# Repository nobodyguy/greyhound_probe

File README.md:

# Greyhound probe
Greyhound probe is a fast and efficient Black Magic Probe compatible programmer and debugger

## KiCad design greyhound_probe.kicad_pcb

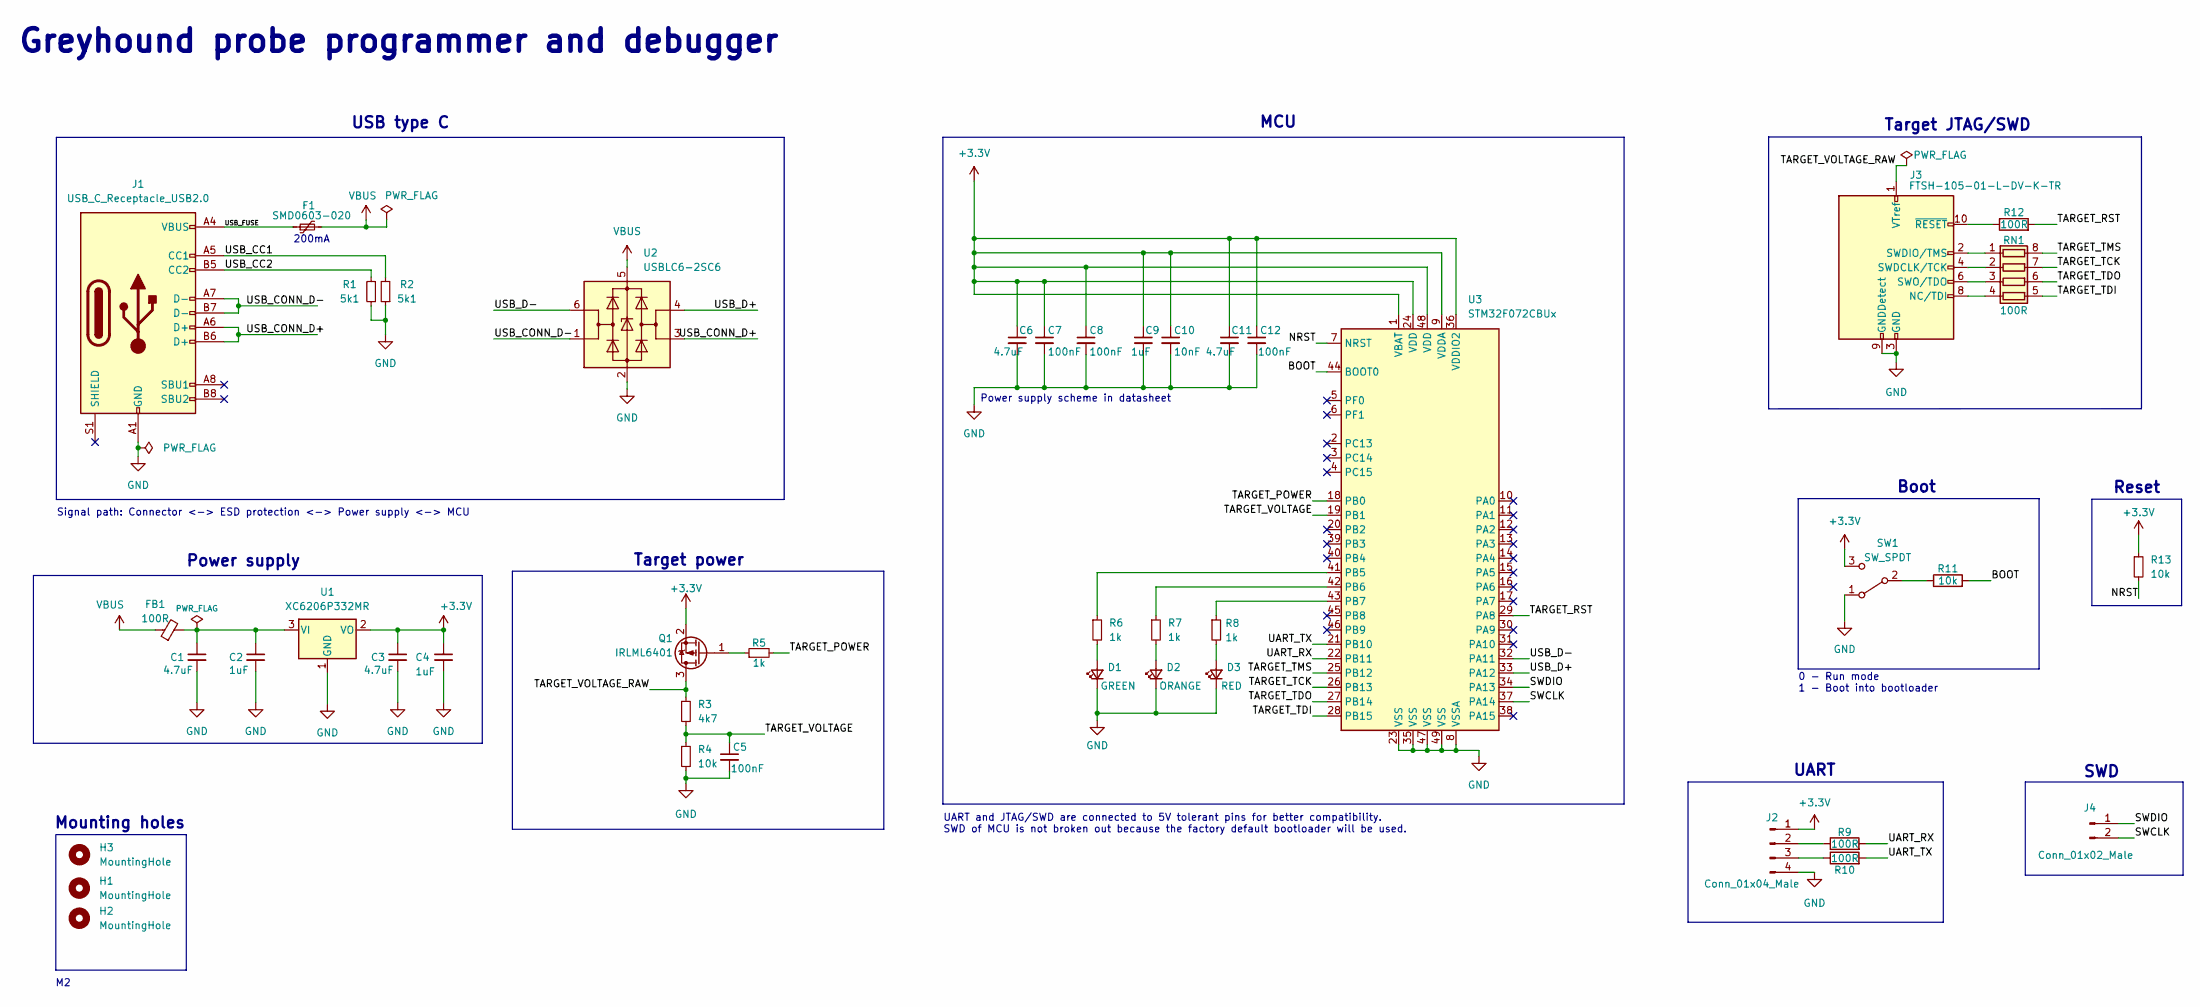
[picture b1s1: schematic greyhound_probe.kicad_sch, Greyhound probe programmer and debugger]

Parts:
C1, C3: 4.7uF; C_0603_1608Metric; LCSC Part C1592
C2, C4, C9: 1uF; C_0603_1608Metric; LCSC Part C1592
C5, C7, C8, C12: 100nF; C_0603_1608Metric; LCSC Part C66501
C6, C11: 4.7uF; C_0603_1608Metric; LCSC Part C8032
C10: 10nF; C_0603_1608Metric; LCSC Part C1589
D1: GREEN; D_0603_1608Metric; LCSC Part C72043
D2: ORANGE; D_0603_1608Metric; LCSC Part C146215
D3: RED; D_0603_1608Metric; LCSC Part C72044
F1: SMD0603-020; Fuse_0603_1608Metric; LCSC Part C2760255
FB1: 100R; L_0603_1608Metric; LCSC Part C74325
H1, H2, H3: MountingHole; MountingHole_2.2mm_M2
J1: USB_C_Receptacle_USB2.0; USB_C_Receptacle_HRO_TYPE-C-31-M-12; LCSC Part C165948
J2: Conn_01x04_Male; PinHeader_1x04_P2.54mm_Vertical; LCSC Part C2935910
J3: FTSH-105-01-L-DV-K-TR; PinHeader_2x05_P1.27mm_Vertical_SMD; LCSC Part C448647
J4: Conn_01x02_Male; PinHeader_1x02_P2.54mm_Vertical
Q1: IRLML6401; SOT-23; LCSC Part C518776
R1, R2: 5k1; R_0603_1608Metric; LCSC Part C105580
R3: 4k7; R_0603_1608Metric; LCSC Part C105428
R4, R13: 10k; R_0603_1608Metric
R5, R6, R7, R8: 1k; R_0603_1608Metric; LCSC Part C22548
R9, R10, R12: 100R; R_0603_1608Metric; LCSC Part C105588
R11: 10k; R_0603_1608Metric; LCSC Part C99198
RN1: 100R; R_Array_Convex_4x0603; LCSC Part C25506
SW1: SW_SPDT; SW_SPDT_PCM12; LCSC Part C514016
U1: XC6206P332MR; SOT-23; LCSC Part C5446
U2: USBLC6-2SC6; SOT-23-6; LCSC Part C2827654
U3: STM32F072CBUx; QFN-48-1EP_7x7mm_P0.5mm_EP5.6x5.6mm; LCSC Part C2054107

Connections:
+3.3V: C3.1, C4.1, C6.1, C7.1, C8.1, C9.1, C10.1, C11.1, C12.1, J2.1, Q1.2 (S), R13.1, SW1.3 (C), U1.2 (VO), U3.1 (VBAT), U3.9 (VDDA), U3.24 (VDD), U3.36 (VDDIO2), U3.48 (VDD)
/BOOT: R11.2, U3.44 (BOOT0)
/NRST: R13.2, U3.7 (NRST)
/SWCLK: J4.2, U3.37 (PA14)
/SWDIO: J4.1, U3.34 (PA13)
/TARGET_POWER: R5.2, U3.18 (PB0)
/TARGET_RST: R12.2, U3.29 (PA8)
/TARGET_TCK: RN1.7 (R2.2), U3.26 (PB13)
/TARGET_TDI: RN1.5 (R4.2), U3.28 (PB15)
/TARGET_TDO: RN1.6 (R3.2), U3.27 (PB14)
/TARGET_TMS: RN1.8 (R1.2), U3.25 (PB12)
/TARGET_VOLTAGE: C5.1, R3.2, R4.1, U3.19 (PB1)
/TARGET_VOLTAGE_RAW: J3.1 (VTref), Q1.3 (D), R3.1
/UART_RX: R9.2, U3.22 (PB11)
/UART_TX: R10.2, U3.21 (PB10)
/USB_CC1: J1.A5 (CC1), R2.2
/USB_CC2: J1.B5 (CC2), R1.2
/USB_CONN_D+: J1.A6 (D+), J1.B6 (D+), U2.3 (I/O2)
/USB_CONN_D-: J1.A7 (D-), J1.B7 (D-), U2.1 (I/O1)
/USB_D+: U2.4 (I/O2), U3.33 (PA12)
/USB_D-: U2.6 (I/O1), U3.32 (PA11)
/USB_FUSE: F1.1, J1.A4 (VBUS), J1.A9 (VBUS), J1.B4 (VBUS), J1.B9 (VBUS)
GND: C1.2, C2.2, C3.2, C4.2, C5.2, C6.2, C7.2, C8.2, C9.2, C10.2, C11.2, C12.2, D1.1 (K), D2.1 (K), D3.1 (K), J1.A1 (GND), J1.A12 (GND), J1.B1 (GND), J1.B12 (GND), J2.4, J3.3 (GND), J3.5 (GND), J3.9 (GNDDetect), R1.1, R2.1, R4.2, SW1.1 (A), U1.1 (GND), U2.2 (GND), U3.8 (VSSA), U3.23 (VSS), U3.35 (VSS), U3.47 (VSS), U3.49 (VSS)
unnamed: C1.1, C2.1, FB1.2, U1.3 (VI)
unnamed: D1.2 (A), R6.2
unnamed: D2.2 (A), R7.2
unnamed: D3.2 (A), R8.2
unnamed: J2.2, R9.1
unnamed: J2.3, R10.1
unnamed: J3.2 (SWDIO/TMS), RN1.1 (R1.1)
unnamed: J3.4 (SWDCLK/TCK), RN1.2 (R2.1)
unnamed: J3.6 (SWO/TDO), RN1.3 (R3.1)
unnamed: J3.8 (NC/TDI), RN1.4 (R4.1)
unnamed: J3.10 (~RESET), R12.1
unnamed: Q1.1 (G), R5.1
unnamed: R6.1, U3.41 (PB5)
unnamed: R7.1, U3.42 (PB6)
unnamed: R8.1, U3.43 (PB7)
unnamed: R11.1, SW1.2 (B)
VBUS: F1.2, FB1.1, U2.5 (VBUS)

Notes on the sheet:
Boot
Reset
Power supply
200mA
Greyhound probe programmer and debugger
Target power
0 - Run mode 1 - Boot into bootloader
UART
MCU
Signal path: Connector <-> ESD protection <-> Power supply <-> MCU
SWD
Target JTAG/SWD
Power supply scheme in datasheet
Mounting holes
UART and JTAG/SWD are connected to 5V tolerant pins for better compatibility. SWD of MCU is not broken out because the factory default bootloader will be used.
USB type C

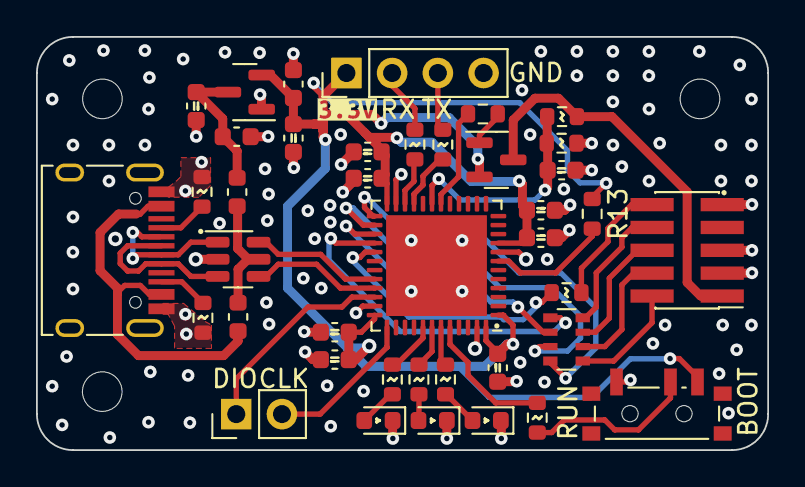
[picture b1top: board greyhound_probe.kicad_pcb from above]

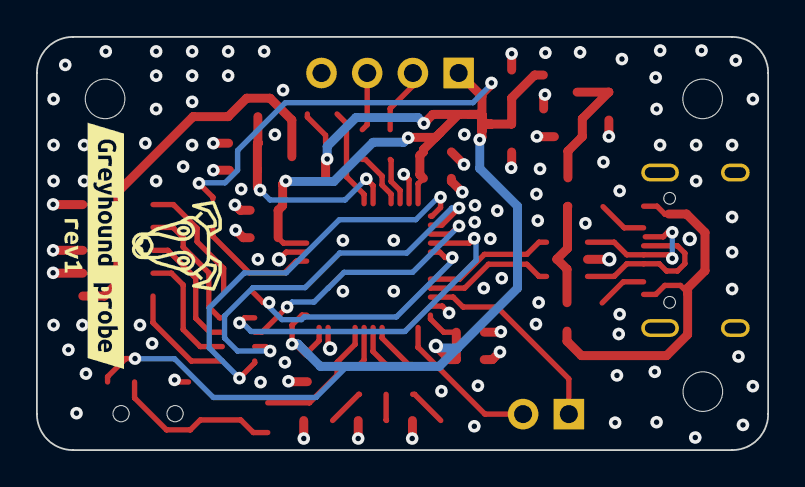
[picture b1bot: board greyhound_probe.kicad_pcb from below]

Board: 4 copper layers, 40.6 x 23.0 mm, 46 parts (2 on the bottom side), 40 nets.

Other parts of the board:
kibuzzard-6360FEA6: G***; kibuzzard-6360FEA6
kibuzzard-63127F62: G***; kibuzzard-63127F62
kibuzzard-63139EF8: G***; kibuzzard-63139EF8

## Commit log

2022-08-19 Initial schematic - USB, power supply and MCU decoupling
2022-08-21 Power supply rework, jtag connector finished
2022-08-23 Led resistors changed, boot button
2022-08-31 Added UART, started with PCB sectioning
2022-09-01 Fixed short and power symbols
2022-09-02 PCB positioning changes, silkscreen changes
2022-09-02 Routing mostly done, rough board outline
2022-09-03 Routed the rest of pins, rounded corners, mounting holes placing
2022-09-03 Added silkscreen labels
2022-09-04 Via stitching done
2022-09-04 LED vias moved a bit farther from silkscreen
2022-09-09 Better spacing of a few signal traces and vias
2022-09-09 Added iBOM
2022-11-01 Added SWD, rearranged bottom part
2022-11-03 Added in series resistor to mosfet gate, nrst pullup, more regulator caps, reduced via sharing
